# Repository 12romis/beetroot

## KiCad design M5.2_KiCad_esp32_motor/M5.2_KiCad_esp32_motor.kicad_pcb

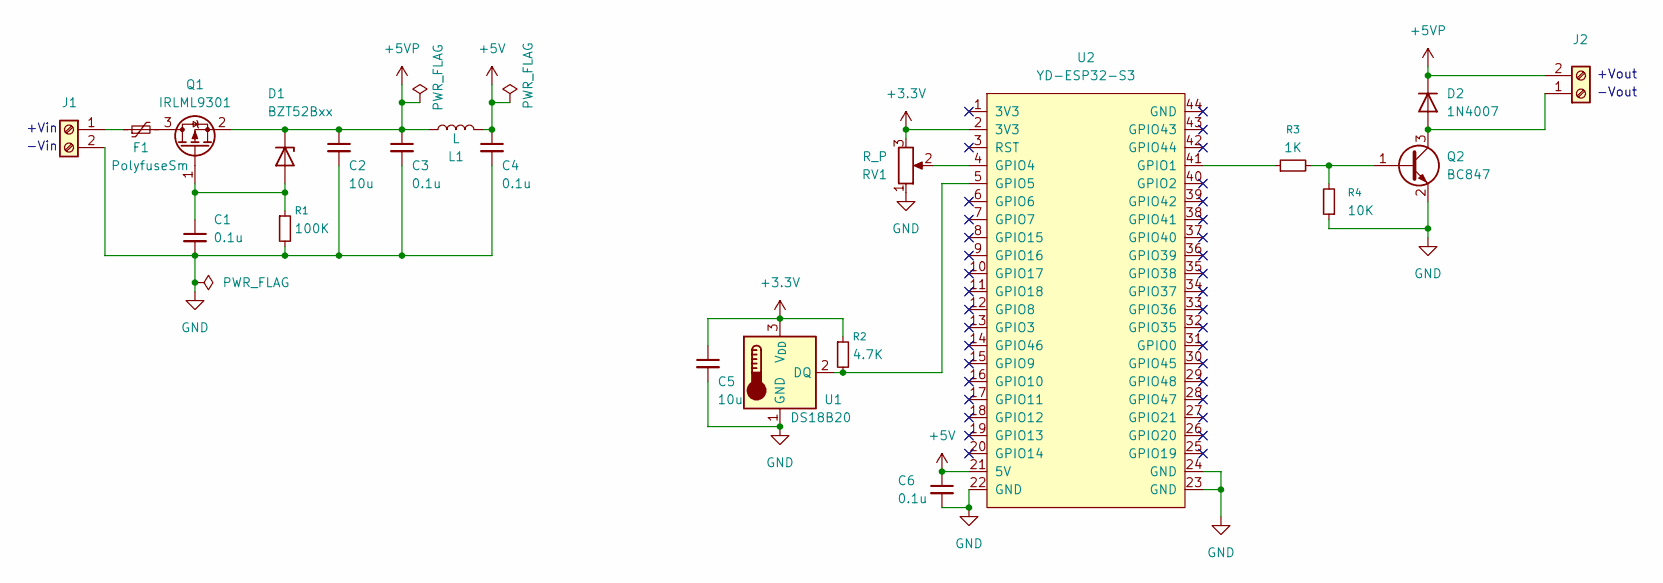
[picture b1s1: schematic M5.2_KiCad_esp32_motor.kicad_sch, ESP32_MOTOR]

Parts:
C1, C3, C4, C6: 0.1u; C_0805_2012Metric
C2, C5: 10u; C_0805_2012Metric
D1: BZT52Bxx; D_SOD-123F
D2: 1N4007; D_DO-41_SOD81_P10.16mm_Horizontal
F1: PolyfuseSm; Fuse_Bourns_MF-SM_7.98x5.44mm
J1, J2: Screw_Terminal_01x02; TerminalBlock_Phoenix_MKDS-1,5-2-5.08_1x02_P5.08mm_Horizont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
L1: L; L_0805_2012Metric
Q1: IRLML9301; SOT-23
Q2: BC847; SOT-23
R1: 100K; R_0805_2012Metric
R2: 4.7K; R_0805_2012Metric
R3: 1K; R_0805_2012Metric
R4: 10K; R_0805_2012Metric
RV1: R_P; Potentiometer_ACP_CA6-VSMD_Vertical
U1: DS18B20; TO-92_Inline
U2: YD-ESP32-S3

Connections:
+3.3V: C5.1, R2.1, RV1.3, U1.3 (V_{DD}), U2.2 (3V3)
+5V: C4.1, C6.1, L1.2, U2.21 (5V)
+5VP: C2.1, C3.1, D1.1 (K), D2.1 (K), J2.2, L1.1, Q1.2 (S)
GND: C1.2, C2.2, C3.2, C4.2, C5.2, C6.2, J1.2, Q2.2 (E), R1.2, R4.1, RV1.1, U1.1 (GND), U2.22 (GND), U2.23 (GND), U2.24 (GND)
unnamed: C1.1, D1.2 (A), Q1.1 (G), R1.1
unnamed: D2.2 (A), J2.1, Q2.3 (C)
unnamed: F1.1, J1.1
unnamed: F1.2, Q1.3 (D)
unnamed: Q2.1 (B), R3.2, R4.2
unnamed: R2.2, U1.2 (DQ), U2.5 (GPIO5)
unnamed: R3.1, U2.41 (GPIO1)
unnamed: RV1.2, U2.4 (GPIO4)

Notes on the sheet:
+Vout
+Vin
-Vin
-Vout

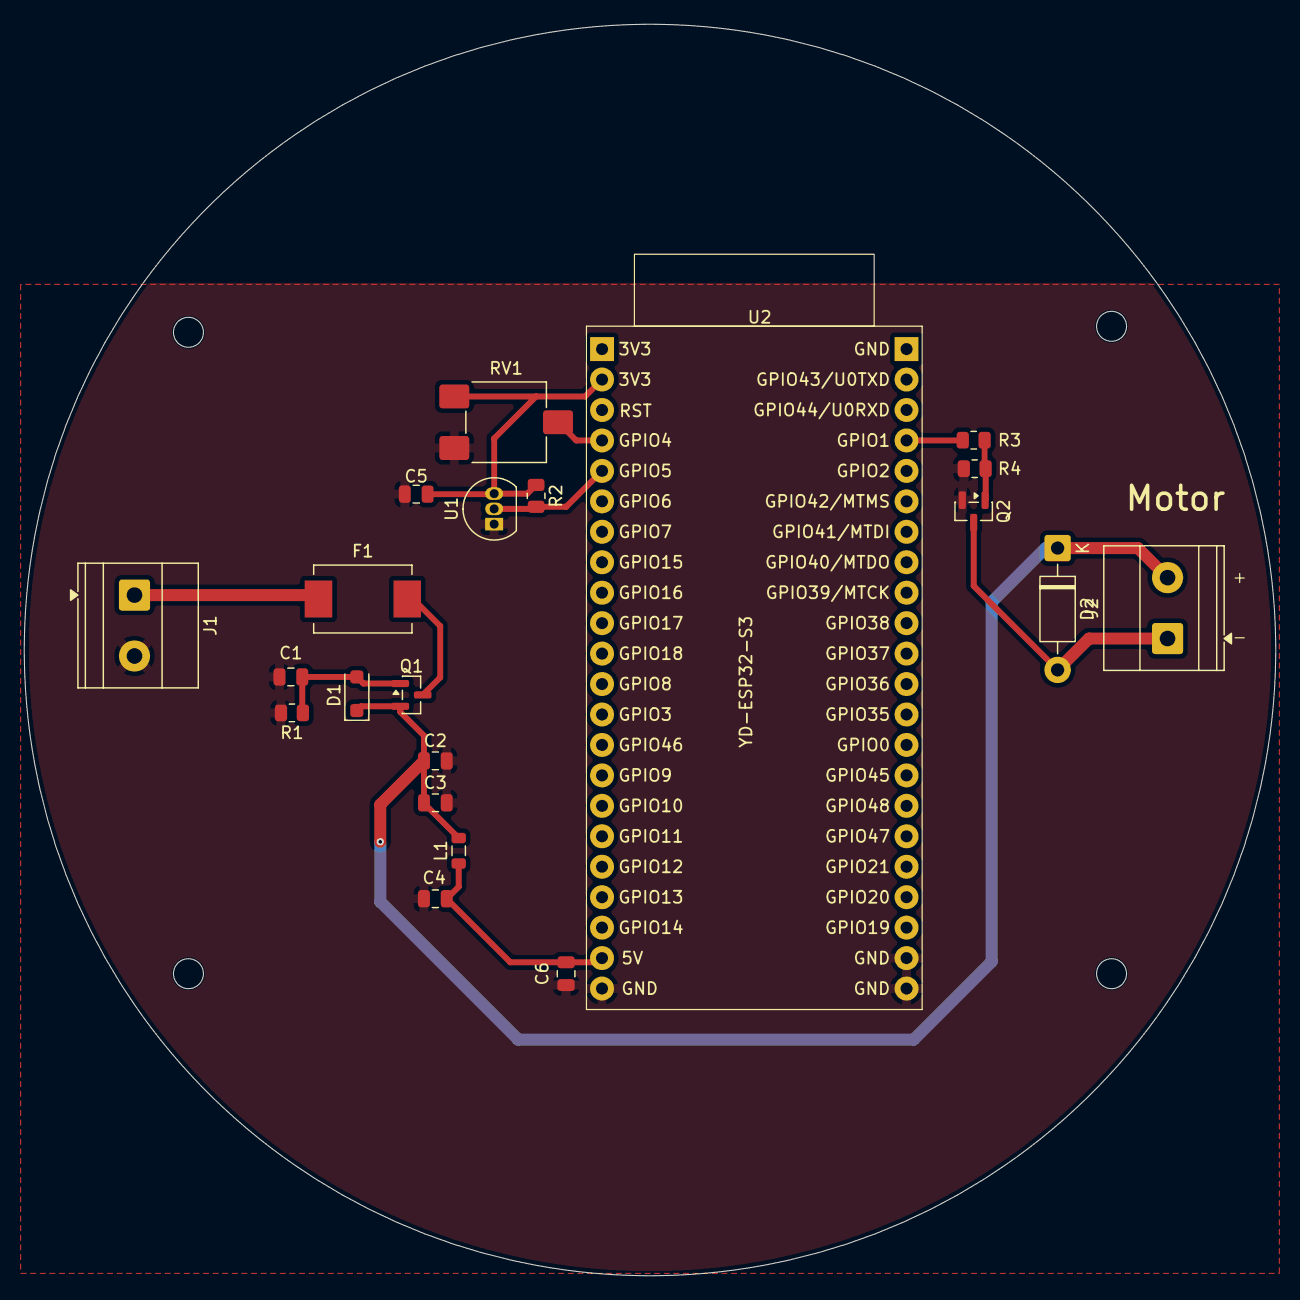
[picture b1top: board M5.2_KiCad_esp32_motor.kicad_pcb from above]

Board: 2 copper layers, 104.4 x 104.4 mm, 21 parts (0 on the bottom side), 12 nets.

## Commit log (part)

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2026-05-25 blinks
2026-05-27 buttons + potentiometr
2026-05-31 hw1.4, L1.5
2026-06-08 Alert and disable rele if temperature is hight
2026-06-19 L2.3_hw
2026-06-20 Blinks and button based on classes, ISR
2026-06-20 measure avg time to relay switch
2026-06-20 pot_motor_pwm
2026-06-27 work
2026-06-27 hw2.5 timer
2026-06-28 esp-idf
2026-06-28 esp-idf interruption
2026-06-29 miniproject TrafficLight
